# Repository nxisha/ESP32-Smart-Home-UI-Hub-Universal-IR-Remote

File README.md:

ESP32 Smart Home UI Hub & Universal IR/BLE Remote

A physical demonstration of the Smart Hub navigating Fire TV via BLE and operating Voltas/Hitachi HVAC units via synthesized IR pulses.

Architecture Overview

A centralized smart home control terminal built around an ESP32-WROOM-32 and a 2.8-inch TFT SPI touch display. This hub unifies control over disparate home appliances by bridging Infrared (IR), Bluetooth Low Energy (BLE), and Wi-Fi protocols into a single concurrent interface.

It actively operates a dual-role BLE architecture—acting as a Server (HID Keyboard) for streaming devices, and a Client for reverse-engineered smart lighting control, bypassing proprietary commercial hubs.

Hardware Stack

MCU: ESP32-WROOM-32 Development Board (Tensilica Xtensa Dual-Core 32-bit LX6)

Display Interface: 2.8" TFT LCD Touch Screen (ILI9341 Driver, XPT2046 Touch Controller)

IR Subsystem: 940nm Infrared LED with current-limiting 220Ω series resistor

Power Architecture:

2x 350mAh 3.7V LiPo Batteries (Parallel configuration for 700mAh capacity)

TP4056 Lithium Battery Charger IC (1A regulated input)

1N4007 Diode (Voltage step-down regulation)

GPIO Pinout & Wiring

Peripheral / Component

ESP32 GPIO

Notes / Alternate Function

TFT_MOSI

GPIO 23

VSPI MOSI

TFT_MISO

GPIO 19

VSPI MISO

TFT_SCLK

GPIO 18

VSPI CLK

TFT_CS

GPIO 15

Chip Select

TFT_DC

GPIO 2

Data/Command

TFT_RST

GPIO 4

Hardware Reset

TOUCH_CS

GPIO 21

Touch Controller CS

IR_TX

GPIO 12

PWM Carrier Generation (38kHz)

Power Subsystem & Diode Regulation

Due to the high transient current spikes required by active IR transmission and the TFT backlight, power is handled via a direct parallel battery array, intentionally bypassing switching buck converters to maximize discharge utilization:

Cell Configuration: Wired in parallel yielding 3.7V nominal @ 700mAh.

Voltage Stepping: Battery positive is routed through a physical SPST switch and into the Anode of a 1N4007 diode.

Logic Leveling: The Cathode drops the 4.2V peak charge by ~0.7V (Forward Voltage Drop), delivering a safe ~3.5V to the ESP32 3V3 pin and TFT VIN, operating safely within absolute maximum ratings without converter switching noise.

Proof of Hardware

View KiCad Schematic / Wiring Diagram

View Logic Analyzer Trace (38kHz IR Carrier)

Build & Flash Instructions

1. IDE Configuration

Environment: Arduino IDE 2.x or PlatformIO

Board: ESP32 Dev Module

Partition Scheme: Huge APP (3MB No OTA/1MB SPIFFS) (Required due to BLE + TFT library overhead).

2. Dependencies

TFT_eSPI by Bodmer (Must configure User_Setup.h for ILI9341 and assigned VSPI pins).

IRremoteESP8266 by crankyoldgit.

BleKeyboard by T-vK.

3. Syska BLE Configuration

To interface directly with the Syska Smart LED without the manufacturer app, configure the target MAC address in ESP32_Smart_Remote.ino:

// Update to target Syska Bulb MAC Address
BLEAddress bulbAddress("11:22:33:44:55:66"); 

4. Compilation

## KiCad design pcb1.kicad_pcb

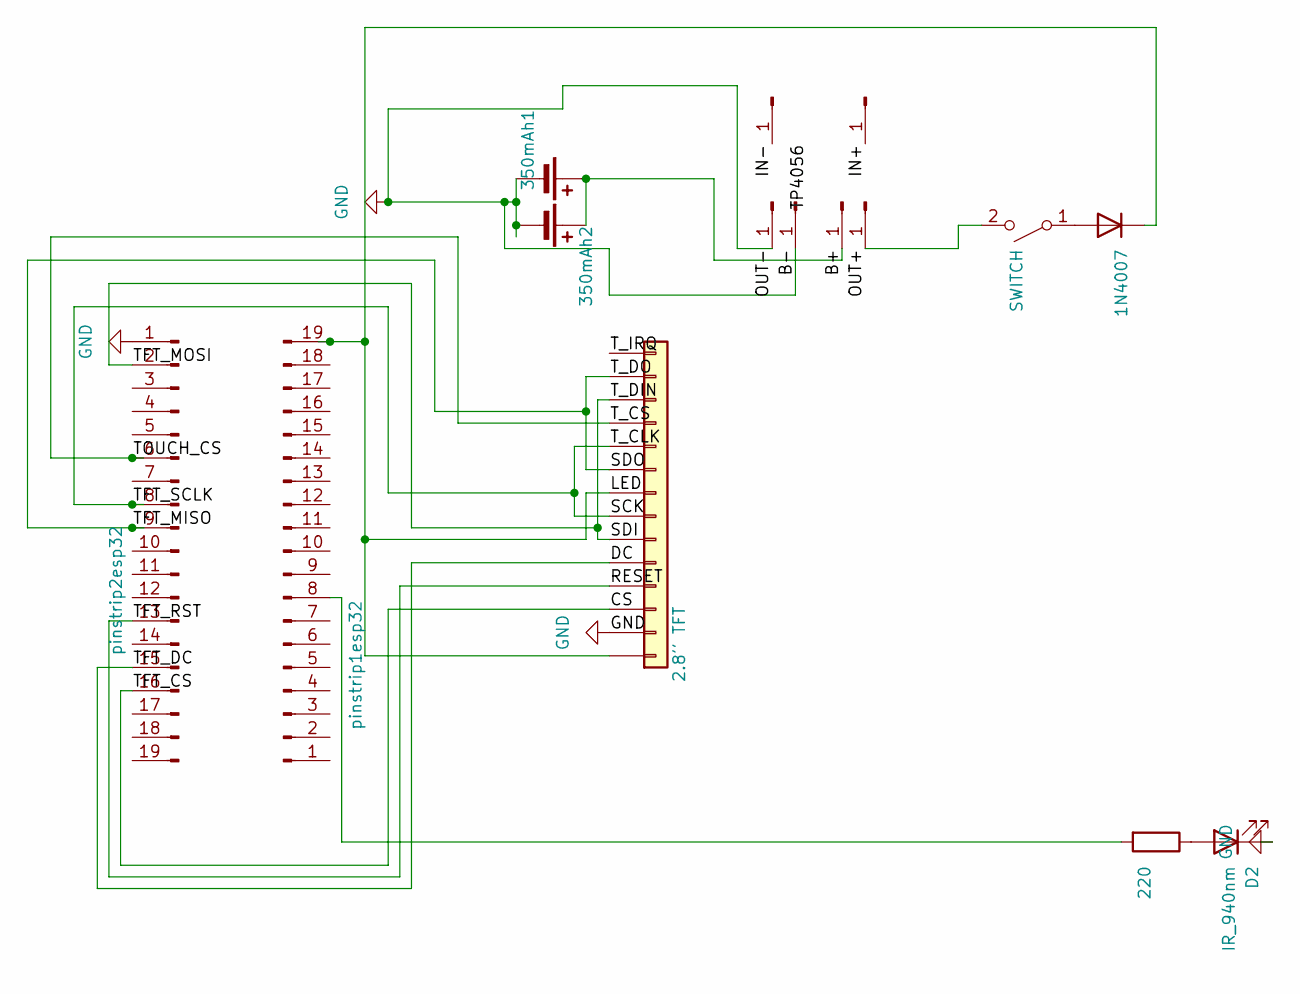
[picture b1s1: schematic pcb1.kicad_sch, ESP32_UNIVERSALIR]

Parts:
1N4007: D; D_DO-41_SOD81_P10.16mm_Horizontal
350mAh1, 350mAh2: Battery_Cell; PinSocket_1x02_P2.54mm_Vertical
D2: IR_940nm; LED_D5.0mm
J2, J4, J5, J6, J7, J8: Conn_01x01_Pin; PinHeader_1x01_P2.54mm_Vertical
R1: 220; R_Axial_DIN0207_L6.3mm_D2.5mm_P10.16mm_Horizontal
SW1: SWITCH; PinHeader_1x02_P2.54mm_Vertical
TFT1: 2.8'' TFT; PinSocket_1x14_P2.54mm_Vertical
pinstrip1esp32, pinstrip2esp32: Conn_01x19_Pin; PinSocket_1x19_P2.54mm_Vertical

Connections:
/B+: 350mAh1.1 (+), 350mAh2.1 (+), J4.1 (Pin_1_1)
/CS: TFT1.3, pinstrip2esp32.16
/DC: TFT1.5, pinstrip2esp32.15
/IN+: J8.1 (Pin_1_1)
/IN-: J7.1 (Pin_1_1)
/LED: 1N4007.1 (K), TFT1.1, TFT1.8, pinstrip1esp32.19
/OUT+: J2.1 (Pin_1_1), SW1.2 (B)
/RESET: TFT1.4, pinstrip2esp32.13
/SCK: TFT1.7, TFT1.10, pinstrip2esp32.8
/SDI: TFT1.6, TFT1.12, pinstrip2esp32.2
/SDO: TFT1.9, TFT1.13, pinstrip2esp32.9
/TOUCH_CS: TFT1.11, pinstrip2esp32.6
/T_IRQ: TFT1.14
GND: 350mAh1.2 (-), 350mAh2.2 (-), D2.1 (K), J5.1 (Pin_1_1), J6.1 (Pin_1_1), TFT1.2, pinstrip2esp32.1
unnamed: 1N4007.2 (A), SW1.1 (A)
unnamed: D2.2 (A), R1.1
unnamed: R1.2, pinstrip1esp32.8

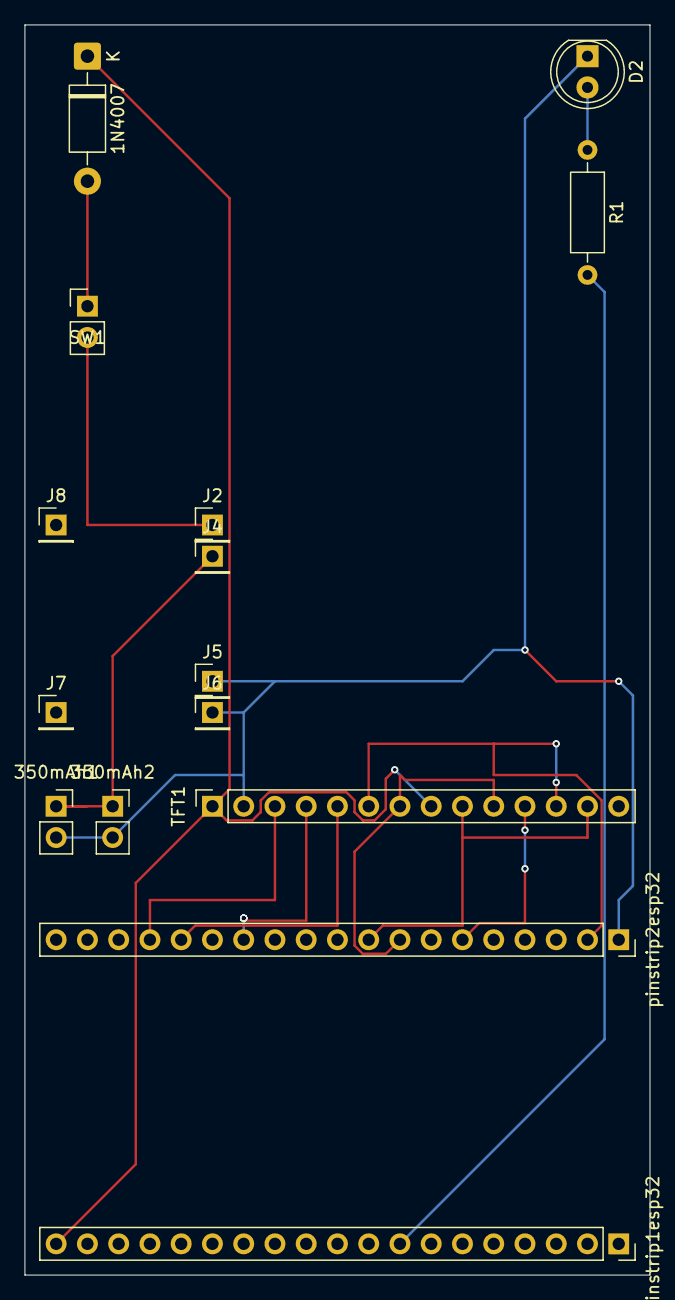
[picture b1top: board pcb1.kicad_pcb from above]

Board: 2 copper layers, 50.8 x 101.6 mm, 15 parts (0 on the bottom side), 14 nets.
